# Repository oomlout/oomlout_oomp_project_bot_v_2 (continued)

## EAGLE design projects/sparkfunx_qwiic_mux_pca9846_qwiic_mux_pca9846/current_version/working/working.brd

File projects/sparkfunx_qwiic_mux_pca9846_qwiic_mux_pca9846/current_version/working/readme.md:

# qwiic_mux_pca9846
 
## summary 
* id: sparkfunx_qwiic_mux_pca9846_qwiic_mux_pca9846
* user: sparkfunx
* name: qwiic_mux_pca9846
* board: qwiic_mux_pca9846
* repo: https://github.com/sparkfunX/Qwiic_Mux_PCA9846

* src_file_repo_sch: 
* src_file_repo_sch_link: https://github.com/sparkfunX/Qwiic_Mux_PCA9846/tree/main/
* full details link: https://github.com/oomlout/oomlout_oomp_project_bot_v_2/tree/main/projects/sparkfunx_qwiic_mux_pca9846_qwiic_mux_pca9846/current_version/working

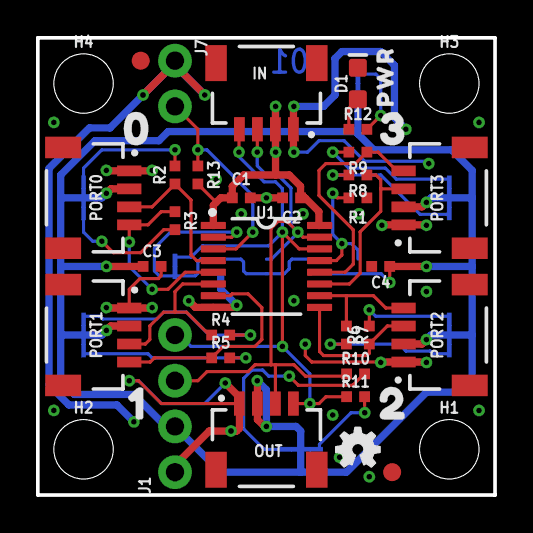
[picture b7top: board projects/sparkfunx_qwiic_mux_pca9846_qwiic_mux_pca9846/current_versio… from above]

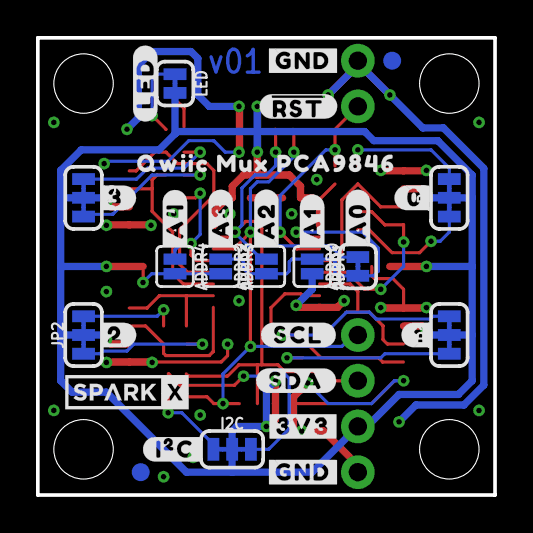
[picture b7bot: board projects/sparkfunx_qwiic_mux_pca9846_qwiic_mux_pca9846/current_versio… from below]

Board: 2 copper layers, 25.4 x 25.4 mm, 73 parts (32 on the bottom side), 27 nets.

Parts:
ADDR0: JUMPER-SMT_2_NC_TRACE_SILK; SMT-JUMPER_2_NC_TRACE_SILK
ADDR1, ADDR2, ADDR3, ADDR4: JUMPER-SMT_2_NO_SILK; SMT-JUMPER_2_NO_SILK
C1, C3, C4: 2.2uF; 0402-TIGHT
C2: 0.1uF; 0402-TIGHT
D1: RED; LED-0603
FD1, FD2, FD3, FD4: FIDUCIAL1X2; FIDUCIAL-1X2
FRAME1: FRAME-LETTER; CREATIVE_COMMONS
H1, H2, H3, H4: STAND-OFF
I2C: JUMPER-SMT_3_2-NC_TRACE_SILK; SMT-JUMPER_3_2-NC_TRACE_SILK
IN: QWIIC_RIGHT_ANGLE; JST04_1MM_RA
J1: 1X04_NO_SILK
J7: 1X02_NO_SILK
JP0, JP1, JP2, JP3: JUMPER-SMT_3_2-NC_TRACE_SILK; SMT-JUMPER_3_2-NC_TRACE_SILK
LED: JUMPER-SMT_2_NC_TRACE_SILK; SMT-JUMPER_2_NC_TRACE_SILK
LOGO1: SPECIAL_INSTRUCTIONS-ORDERING; ORDERING_INSTRUCTIONS
LOGO4: OSHW-LOGOMINI; OSHW-LOGO-MINI
OUT: QWIIC_RIGHT_ANGLE; JST04_1MM_RA
PORT0, PORT1, PORT2, PORT3: QWIIC_RIGHT_ANGLE; JST04_1MM_RA
R1, R13: 100k; 0402-TIGHT
R2, R3, R4, R5, R6, R7, R8, R9, R10, R11: 2.2k; 0402-TIGHT
R12: 1k; 0402-TIGHT
U1: PCA9846; SOT403-1
U$1: SPARKX-LOGO3; SPARKX-SMALL
U$2: PWR43214
U$3: 043215
U$4: 10
U$5: 211
U$6: 3212
U$7: ##RST##8
U$8: #0#9
U$9: #1#9
U$10: #2#9
U$11: #3#9
U$12: #3V3#7
U$13: #A0#0
U$14: #A1#1
U$15: #A2#2
U$16: #A3#3
U$17: #A4#4
U$18, U$19: #GND#7
U$21: #SCL#5
U$22: #SDA#6
U$23: #LED#0
U$24: QWIIC_MUX_PCA98461
U$25: #I�C#0

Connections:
3.3V: ADDR3.2, ADDR4.2, C1.1, C2.1, C3.1, C4.1, I2C.2, IN.2, J1.2, JP0.2, JP1.2, JP2.2, JP3.2, LED.2, OUT.2, PORT0.2, PORT1.2, PORT2.2, PORT3.2, R13.2, U1.1, U1.16
!RESET!: J7.2, R13.1, U1.3
A0: ADDR0.1, ADDR1.1, ADDR2.1, ADDR3.1, U1.2
A1: ADDR4.1, R1.2, U1.13
GND: ADDR1.2, C1.2, C2.2, C3.2, C4.2, D1.C, IN.1, J1.1, J7.1, OUT.1, PORT0.1, PORT1.1, PORT2.1, PORT3.1, R1.1, U1.8
unnamed: JP0.3, R2.2
unnamed: JP0.1, R3.2
unnamed: JP1.3, R4.2
unnamed: JP1.1, R5.2
unnamed: JP2.3, R6.2
unnamed: JP2.1, R7.2
unnamed: JP3.3, R8.2
unnamed: JP3.1, R9.2
unnamed: I2C.3, R10.2
unnamed: I2C.1, R11.2
unnamed: LED.1, R12.2
unnamed: D1.A, R12.1
SC0: PORT0.4, R3.1, U1.5
SC1: PORT1.4, R5.1, U1.7
SC2: PORT2.4, R7.1, U1.10
SC3: PORT3.4, R9.1, U1.12
SCL: ADDR0.2, IN.4, J1.4, OUT.4, R11.1, U1.14
SD0: PORT0.3, R2.1, U1.4
SD1: PORT1.3, R4.1, U1.6
SD2: PORT2.3, R6.1, U1.9
SD3: PORT3.3, R8.1, U1.11
SDA: ADDR2.2, IN.3, J1.3, OUT.3, R10.1, U1.15
